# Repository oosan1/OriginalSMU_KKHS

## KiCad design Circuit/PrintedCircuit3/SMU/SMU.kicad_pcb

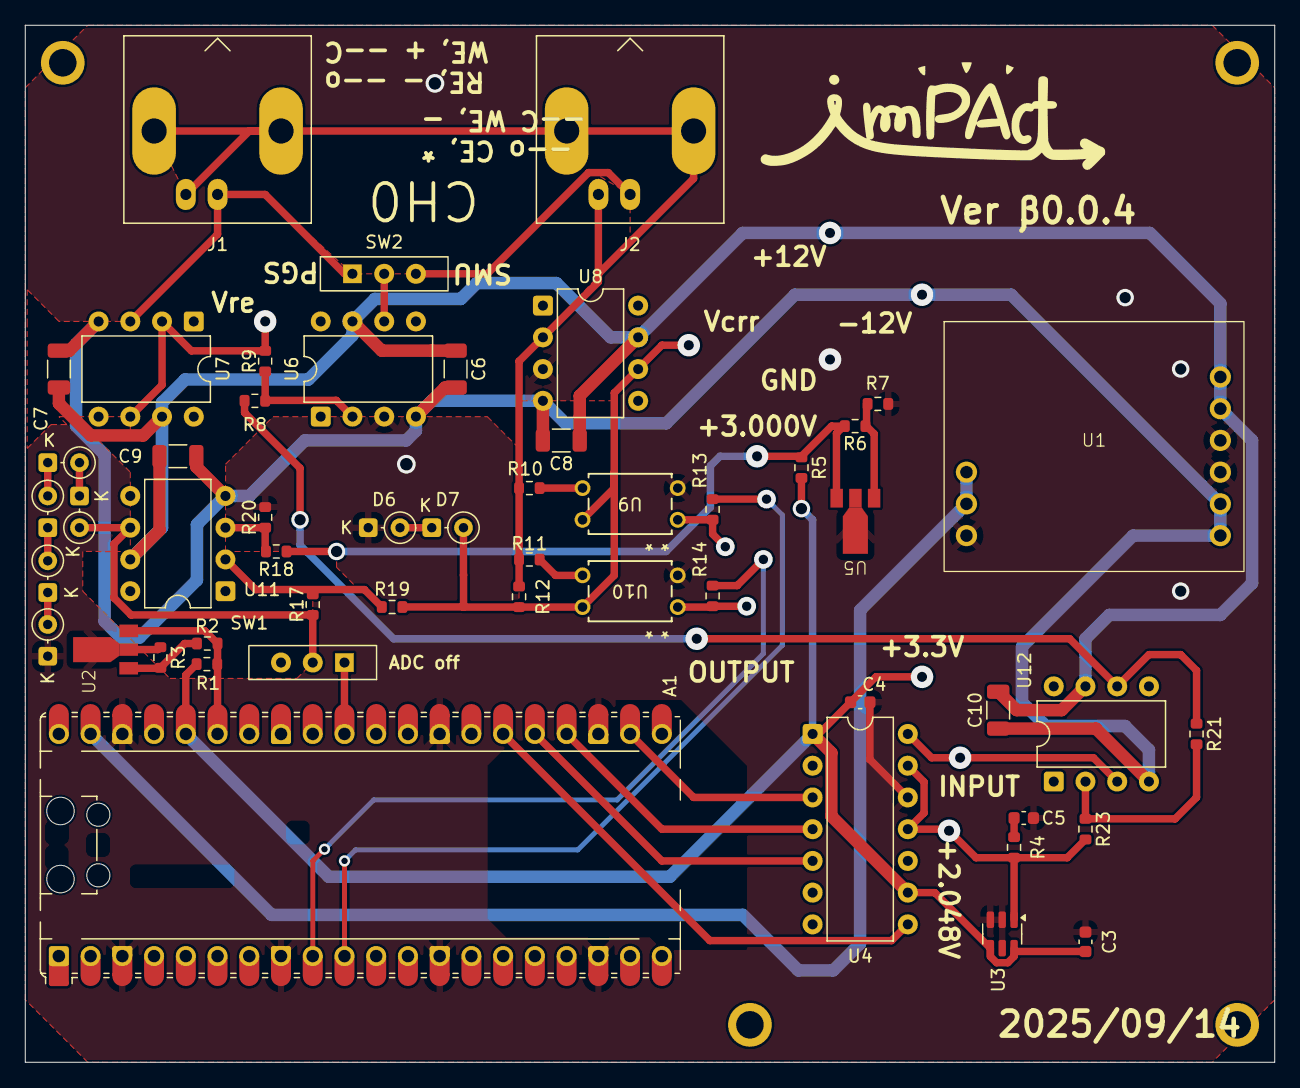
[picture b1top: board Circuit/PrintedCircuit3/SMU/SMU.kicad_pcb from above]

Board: 2 copper layers, 100.0 x 83.0 mm, 52 parts (0 on the bottom side), 40 nets.

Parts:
A1: RaspberryPi_Pico; RaspberryPi_Pico_Common_Unspecified
C3, C4, C5: 2.2u; C_0603_1608Metric
C6, C7, C8, C9, C10: 4.7u; C_1206_3216Metric
D1, D2, D3, D4, D5, D6, D7: D; D_DO-34_SOD68_P2.54mm_Vertical_KathodeUp
J1, J2: Conn_Coaxial; BNC_Amphenol_B6252HB-NPP3G-50_Horizontal
R1, R5: 51; R_0603_1608Metric
R2, R4, R6, R11, R13, R14: 1k; R_0603_1608Metric
R3, R7: 5.1k; R_0603_1608Metric
R8, R9, R12, R17, R19, R20, R21, R23: 10k; R_0603_1608Metric
R10: 100; R_0603_1608Metric
R18: 30k; R_0603_1608Metric
SW1, SW2: SW_SPDT; SW_Slide-03_Wuerth-WS-SLTV_10x2.5x6.4_P2.54mm
U1: TPS65131_kit
U2, U5: NJM1431AU
U3: MCP1501-20xCH; SOT-23-6
U4: MCP4922; DIP-14_W7.62mm
U6, U7, U8, U11, U12: OP07; DIP-8_W7.62mm
U9, U10: TLP241AF; DIP4_TOS

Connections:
3.0V_REF: R5.1, R6.1, R18.1, U5.3 (CATHODE)
+2.048V_REF: R4.1, R23.2, U3.1 (OUT), U4.11 (VrefB), U4.13 (VrefA)
+3.3V: A1.36 (3V3), C3.2, C4.1, R1.2, R5.2, U3.4 (~SHDN), U3.6 (VDD), U4.1 (Vdd), U4.9 (~SHDN)
+12V: C6.1, C7.1, C8.1, C9.2, C10.2, U1.4 (+OUT), U1.5 (+OUT), U6.7 (V+), U7.7 (V+), U8.7 (V+), U11.7 (V+), U12.7 (V+)
-12V: C6.2, C7.2, C8.2, C9.1, C10.1, U1.8 (-OUT), U1.9 (-OUT), U6.4 (V-), U7.4 (V-), U8.4 (V-), U11.4 (V-), U12.4 (V-)
/PotentioStatUnit/CE: SW2.2 (B), U6.6
/PotentioStatUnit/INPUT: R8.1, R21.1, U12.6
/PotentioStatUnit/RE: J1.1 (In), SW2.1 (A), U7.3 (+)
/PotentioStatUnit/Vcrr: D7.2 (A), R12.2, R19.2, U8.6, U9.4, U10.4
/PotentioStatUnit/Vre: R9.1, U7.2 (-), U7.6
/PotentioStatUnit/WE: J1.2 (Ext), J2.2 (Ext), R10.1, R11.1, R12.1, U8.2 (-)
/シフト増幅回路/INPUT: U4.14 (VA), U12.3 (+)
/反転回路/OUTPUT: D5.2 (A), R17.1, SW1.2 (B), U11.6
GND: A1.3 (GND), A1.8 (GND), A1.13 (GND), A1.18 (GND), A1.23 (GND), A1.28 (GND), A1.38 (GND), C3.1, C4.2, C5.1, D1.1 (K), D6.1 (K), R3.1, R7.1, R20.2, U1.3 (GND), U1.6 (GND), U1.7 (GND), U2.2 (ANODE), U3.2 (GND), U3.3 (GND), U3.5 (GND), U4.12 (Vss), U5.2 (ANODE), U6.3 (+), U8.3 (+), U9.2, U10.2
unnamed: A1.35 (ADC_VREF), R1.1, R2.1, U2.3 (CATHODE)
unnamed: A1.22 (GPIO17), U4.3 (~CS)
unnamed: A1.24 (GPIO18), U4.4 (SCK)
unnamed: A1.25 (GPIO19), U4.5 (SDI)
unnamed: A1.26 (GPIO20), U4.8 (~LDAC)
unnamed: A1.31 (GPIO26_ADC0), SW1.1 (A)
unnamed: C5.2, R4.2
unnamed: D1.2 (A), D2.1 (K)
unnamed: D2.2 (A), D3.1 (K)
unnamed: D3.2 (A), D4.1 (K)
unnamed: D4.2 (A), D5.1 (K)
unnamed: D6.2 (A), D7.1 (K)
unnamed: J2.1 (In), SW2.3 (C)
unnamed: R10.2, U9.3
unnamed: R11.2, U10.3
unnamed: R13.1, U9.1
unnamed: R14.1, U10.1
unnamed: R2.2, R3.2, U2.1 (REF)
unnamed: R6.2, R7.2, U5.1 (REF)
unnamed: R8.2, R9.2, U6.2 (-)
unnamed: R18.2, R20.1, U11.3 (+)
unnamed: R17.2, R19.1, U11.2 (-)
unnamed: R21.2, R23.1, U12.2 (-)
VSYS: A1.39 (VSYS), U1.1 (IN+), U1.2 (EN)
x1k: A1.9 (GPIO6), R14.2
x100: A1.10 (GPIO7), R13.2

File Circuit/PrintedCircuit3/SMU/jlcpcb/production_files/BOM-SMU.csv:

Comment,Designator,Footprint,LCSC,Quantity
1k,"R11,R13,R14,R2,R4,R6",R_0603_1608Metric,C21190,6
100,R10,R_0603_1608Metric,C22775,1
30k,R18,R_0603_1608Metric,C22984,1
5.1k,"R3,R7",R_0603_1608Metric,C23186,2
51,"R1,R5",R_0603_1608Metric,C23197,2
2.2u,"C3,C4,C5",C_0603_1608Metric,C23630,3
10k,"R12,R17,R19,R20,R21,R23,R8,R9",R_0603_1608Metric,C25804,8
4.7u,"C10,C6,C7,C8,C9",C_1206_3216Metric,C29823,5
OP07,U11,DIP-8_W7.62mm,,1
TLP241AF,U10,DIP4_TOS,,1
TLP241AF,U9,DIP4_TOS,,1
OP07,U8,DIP-8_W7.62mm,,1
OP07,U7,DIP-8_W7.62mm,,1
OP07,U6,DIP-8_W7.62mm,,1
~,U5,NJM1431AU,,1
MCP4922,U4,DIP-14_W7.62mm,,1
MCP1501-20xCH,U3,SOT-23-6,,1
~,U2,NJM1431AU,,1
TPS65131_kit,U1,TPS65131_kit,,1
SW_SPDT,SW2,SW_Slide-03_Wuerth-WS-SLTV_10x2.5x6.4_P2.54mm,,1
SW_SPDT,SW1,SW_Slide-03_Wuerth-WS-SLTV_10x2.5x6.4_P2.54mm,,1
Conn_Coaxial,J2,BNC_Amphenol_B6252HB-NPP3G-50_Horizontal,,1
Conn_Coaxial,J1,BNC_Amphenol_B6252HB-NPP3G-50_Horizontal,,1
D,D4,D_DO-34_SOD68_P2.54mm_Vertical_KathodeUp,,1
D,D3,D_DO-34_SOD68_P2.54mm_Vertical_KathodeUp,,1
D,D2,D_DO-34_SOD68_P2.54mm_Vertical_KathodeUp,,1
D,D1,D_DO-34_SOD68_P2.54mm_Vertical_KathodeUp,,1
RaspberryPi_Pico,A1,RaspberryPi_Pico_Common_Unspecified,,1
D,D7,D_DO-34_SOD68_P2.54mm_Vertical_KathodeUp,,1
D,D5,D_DO-34_SOD68_P2.54mm_Vertical_KathodeUp,,1
D,D6,D_DO-34_SOD68_P2.54mm_Vertical_KathodeUp,,1
OP07,U12,DIP-8_W7.62mm,,1

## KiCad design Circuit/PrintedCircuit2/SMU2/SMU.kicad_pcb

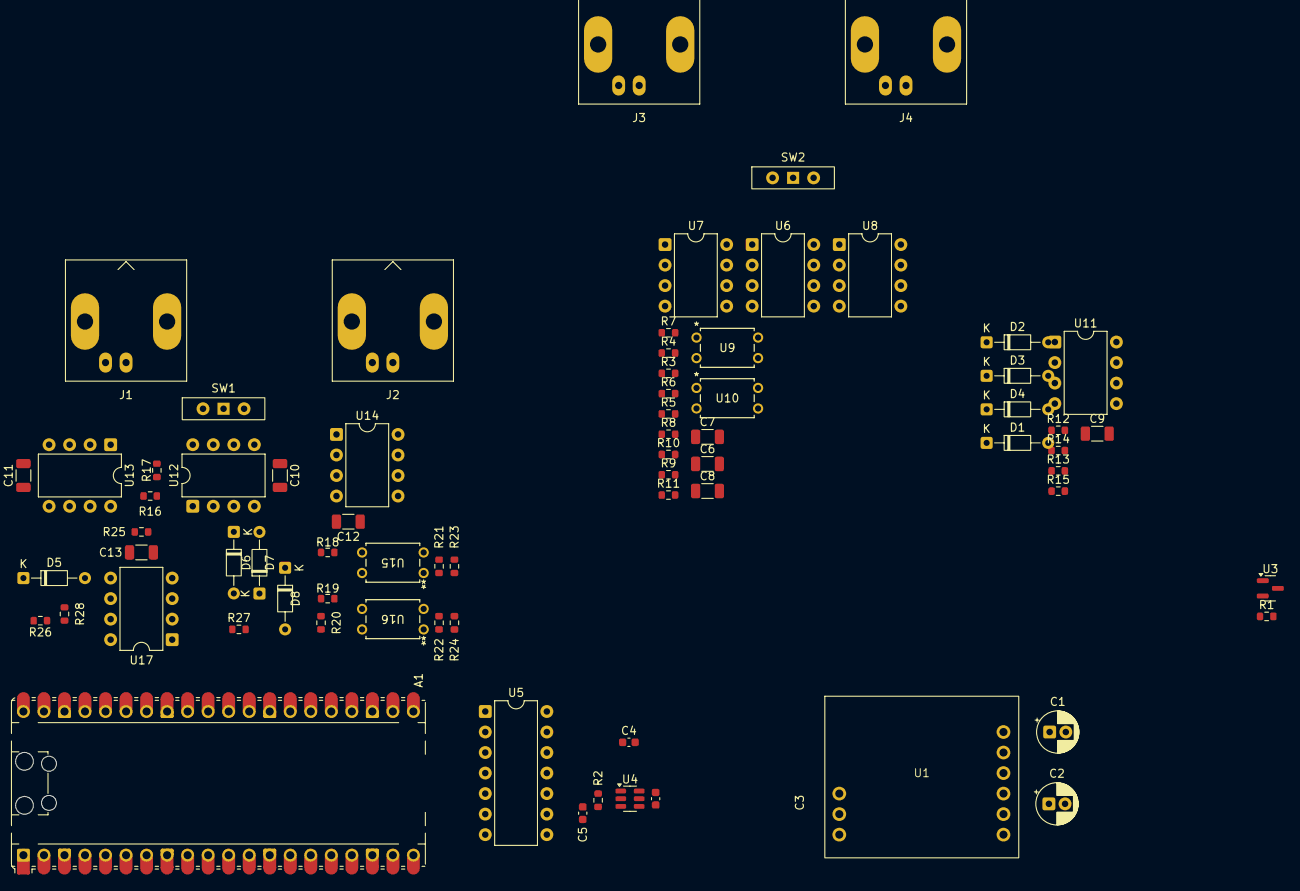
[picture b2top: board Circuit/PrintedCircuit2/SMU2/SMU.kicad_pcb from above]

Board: 6 copper layers, 73 parts (1 on the bottom side), 51 nets, no tracks yet.

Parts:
A1: RaspberryPi_Pico; RaspberryPi_Pico_Common_Unspecified
C1, C2: 100u; CP_Radial_D5.0mm_P2.00mm
C3, C4, C5: 2.2u; C_0603_1608Metric
C6, C7, C8, C9, C10, C11, C12, C13: 4.7u; C_1206_3216Metric
D1, D5: ZeD; D_DO-34_SOD68_P7.62mm_Horizontal
D2, D3, D4, D6, D7, D8: D; D_DO-34_SOD68_P7.62mm_Horizontal
J1, J2, J3, J4: Conn_Coaxial; BNC_Amphenol_B6252HB-NPP3G-50_Horizontal
R1: 200; R_0603_1608Metric
R2, R6, R19: 1k; R_0603_1608Metric
R3, R4, R5, R8, R9, R12, R14, R15, R16, R17, R18, R21, R22, R25, R27, R28: 10k; R_0603_1608Metric
R7, R20: 100; R_0603_1608Metric
R10, R11, R23, R24: 20k; R_0603_1608Metric
R13, R26: 30k; R_0603_1608Metric
SW1, SW2: SW_SPDT; SW_Slide-03_Wuerth-WS-SLTV_10x2.5x6.4_P2.54mm
U1: TPS65131_kit
U2, U3: LM4040DBZ-3; SOT-23
U4: MCP1501-20xCH; SOT-23-6
U5: MCP4922; DIP-14_W7.62mm
U6, U7, U8, U11, U12, U13, U14, U17: OP07; DIP-8_W7.62mm
U9, U10, U15, U16: TLP241AF; DIP4_TOS

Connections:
3.0V_REF: R1.1, R13.1, R26.1, U3.1 (K)
+3.3V: A1.36 (3V3), C3.2, C4.1, R1.2, U4.6 (VDD), U5.1 (Vdd), U5.9 (~SHDN)
+12V: C1.1, C6.1, C7.1, C8.1, C9.2, C10.1, C11.1, C12.1, C13.2, U1.4 (+OUT), U1.5 (+OUT), U6.7 (V+), U7.7 (V+), U8.7 (V+), U11.7 (V+), U12.7 (V+), U13.7 (V+), U14.7 (V+), U17.7 (V+)
-12V: C2.2, C6.2, C7.2, C8.2, C9.1, C10.2, C11.2, C12.2, C13.1, U1.8 (-OUT), U1.9 (-OUT), U6.4 (V-), U7.4 (V-), U8.4 (V-), U11.4 (V-), U12.4 (V-), U13.4 (V-), U14.4 (V-), U17.4 (V-)
/PotentioStatUnit1/CE: SW1.2 (B), U12.6
/PotentioStatUnit1/INPUT: R16.1, U5.14 (VA)
/PotentioStatUnit1/RE: J1.1 (In), SW1.1 (A), U13.3 (+)
/PotentioStatUnit1/Vcrr: D8.2 (A), R20.2, R27.2, U14.6, U15.4, U16.4
/PotentioStatUnit1/Vre: R17.1, U13.2 (-), U13.6
/PotentioStatUnit1/WE: J1.2 (Ext), J2.2 (Ext), R18.1, R19.1, R20.1, U14.2 (-)
/PotentioStatUnit/CE: SW2.2 (B), U6.6
/PotentioStatUnit/INPUT: R3.1, U5.10 (VB)
/PotentioStatUnit/RE: J3.1 (In), SW2.1 (A), U7.3 (+)
/PotentioStatUnit/Vcrr: D4.2 (A), R7.2, R14.2, U8.6, U9.4, U10.4
/PotentioStatUnit/Vre: R4.1, U7.2 (-), U7.6
/PotentioStatUnit/WE: J3.2 (Ext), J4.2 (Ext), R5.1, R6.1, R7.1, U8.2 (-)
/REF_+2.048V: R2.1, U4.1 (OUT), U5.11 (VrefB), U5.13 (VrefA)
/反転回路1/OUTPUT: A1.31 (GPIO26_ADC0), D5.2 (A), R25.1, U17.6
/反転回路/OUTPUT: A1.32 (GPIO27_ADC1), D1.2 (A), R12.1, U11.6
GND: A1.3 (GND), A1.8 (GND), A1.13 (GND), A1.18 (GND), A1.23 (GND), A1.28 (GND), A1.38 (GND), C1.2, C2.1, C3.1, C4.2, C5.1, D1.1 (K), D2.1 (K), D5.1 (K), D6.1 (K), R8.2, R9.1, R15.2, R21.2, R22.1, R28.2, U1.3 (GND), U1.6 (GND), U1.7 (GND), U2.2 (A), U3.2 (A), U4.2 (GND), U4.3 (GND), U4.4 (~SHDN), U4.5 (GND), U5.12 (Vss), U6.3 (+), U8.3 (+), U9.2, U10.2, U12.3 (+), U14.3 (+), U15.2, U16.2
unnamed: A1.35 (ADC_VREF), U2.1 (K)
unnamed: A1.22 (GPIO17), U5.3 (~CS)
unnamed: A1.24 (GPIO18), U5.4 (SCK)
unnamed: A1.25 (GPIO19), U5.5 (SDI)
unnamed: A1.26 (GPIO20), U5.8 (~LDAC)
unnamed: C5.2, R2.2
unnamed: D2.2 (A), D3.1 (K)
unnamed: D3.2 (A), D4.1 (K)
unnamed: D6.2 (A), D7.1 (K)
unnamed: D7.2 (A), D8.1 (K)
unnamed: J2.1 (In), SW1.3 (C)
unnamed: J4.1 (In), SW2.3 (C)
unnamed: R5.2, U9.3
unnamed: R6.2, U10.3
unnamed: R8.1, R10.2, U9.1
unnamed: R9.2, R11.1, U10.1
unnamed: R18.2, U15.3
unnamed: R19.2, U16.3
unnamed: R21.1, R23.2, U15.1
unnamed: R22.2, R24.1, U16.1
unnamed: R3.2, R4.2, U6.2 (-)
unnamed: R13.2, R15.1, U11.3 (+)
unnamed: R12.2, R14.1, U11.2 (-)
unnamed: R16.2, R17.2, U12.2 (-)
unnamed: R26.2, R28.1, U17.3 (+)
unnamed: R25.2, R27.1, U17.2 (-)
VSYS: A1.39 (VSYS), U1.1 (IN+), U1.2 (EN)
x1k_1: A1.9 (GPIO6), R24.2
x1k_2: A1.11 (GPIO8), R11.2
x10k_1: A1.10 (GPIO7), R23.1
x10k_2: A1.12 (GPIO9), R10.1

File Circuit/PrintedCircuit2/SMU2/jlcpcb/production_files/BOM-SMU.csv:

Comment,Designator,Footprint,LCSC,Quantity
1k,"R19,R2,R6",R_0603_1608Metric,C21190,3
100,"R20,R7",R_0603_1608Metric,C22775,2
30k,"R13,R26",R_0603_1608Metric,C22984,2
2.2u,"C3,C4,C5",C_0603_1608Metric,C23630,3
10k,"R12,R14,R15,R16,R17,R18,R21,R22,R25,R27,R28,R3,R4,R5,R8,R9",R_0603_1608Metric,C25804,16
4.7u,"C10,C11,C12,C13,C6,C7,C8,C9",C_1206_3216Metric,C29823,8
20k,"R10,R11,R23,R24",R_0603_1608Metric,C4184,4
OP07,U12,DIP-8_W7.62mm,,1
OP07,U11,DIP-8_W7.62mm,,1
TLP241AF,U10,DIP4_TOS,,1
TLP241AF,U9,DIP4_TOS,,1
OP07,U8,DIP-8_W7.62mm,,1
OP07,U7,DIP-8_W7.62mm,,1
OP07,U6,DIP-8_W7.62mm,,1
MCP4922,U5,DIP-14_W7.62mm,,1
MCP1501-20xCH,U4,SOT-23-6,,1
LM4040DBZ-3,U3,SOT-23,,1
LM4040DBZ-3,U2,SOT-23,,1
TPS65131_kit,U1,TPS65131_kit,,1
SW_SPDT,SW2,SW_Slide-03_Wuerth-WS-SLTV_10x2.5x6.4_P2.54mm,,1
SW_SPDT,SW1,SW_Slide-03_Wuerth-WS-SLTV_10x2.5x6.4_P2.54mm,,1
200,R1,R_0603_1608Metric,,1
Conn_Coaxial,J4,BNC_Amphenol_B6252HB-NPP3G-50_Horizontal,,1
Conn_Coaxial,J3,BNC_Amphenol_B6252HB-NPP3G-50_Horizontal,,1
Conn_Coaxial,J2,BNC_Amphenol_B6252HB-NPP3G-50_Horizontal,,1
Conn_Coaxial,J1,BNC_Amphenol_B6252HB-NPP3G-50_Horizontal,,1
D,D8,D_DO-34_SOD68_P7.62mm_Horizontal,,1
D,D7,D_DO-34_SOD68_P7.62mm_Horizontal,,1
D,D6,D_DO-34_SOD68_P7.62mm_Horizontal,,1
ZeD,D5,D_DO-34_SOD68_P7.62mm_Horizontal,,1
D,D4,D_DO-34_SOD68_P7.62mm_Horizontal,,1
D,D3,D_DO-34_SOD68_P7.62mm_Horizontal,,1
D,D2,D_DO-34_SOD68_P7.62mm_Horizontal,,1
ZeD,D1,D_DO-34_SOD68_P7.62mm_Horizontal,,1
100u,C2,CP_Radial_D5.0mm_P2.00mm,,1
100u,C1,CP_Radial_D5.0mm_P2.00mm,,1
SW_SPDT,SW4,SW_Slide-03_Wuerth-WS-SLTV_10x2.5x6.4_P2.54mm,,1
SW_SPDT,SW3,SW_Slide-03_Wuerth-WS-SLTV_10x2.5x6.4_P2.54mm,,1
TLP241AF,U16,DIP4_TOS,,1
OP07,U14,DIP-8_W7.62mm,,1
OP07,U17,DIP-8_W7.62mm,,1
TLP241AF,U15,DIP4_TOS,,1
OP07,U13,DIP-8_W7.62mm,,1
RaspberryPi_Pico,A1,RaspberryPi_Pico_Common_Unspecified,,1

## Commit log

2025-01-30 webクライアントを追加
2025-01-30 SMUの回路図等を追加
2025-01-30 シリアルの接続処理を追加
2025-01-30 シリアルコンソールの表示部分を追加
2025-01-30 シリアルの書き込み機能を追加
2025-01-30 シリアルの読み取り処理を追加(バグあり)
2025-02-02 SMUの各部分の配線を追加
2025-02-02 各部品の配線が完了。部品表を作り、発注書を作成。
2025-02-10 PWMのテスト用プログラム追加
2025-02-10 シリアル読み込みのバグ除去
2025-02-10 電気化学インピーダンス法用のシミュレーション回路を追加
2025-02-11 ファイル名変更(長すぎるとエラーが出るため)
2025-03-09 シリアル書き込みの不具合を修正
2025-03-09 ファイル構成を変更、シミュレーション用ファイルを追加
2025-03-17 実回路に合わせてシミュレーション回路を調整
2025-03-17 シリアル通信プロトコルに合わせてIVカーブ測定プログラムを変更
2025-03-17 コントロールパネル、グラフエリアを追加 IVカーブの測定、CSV出力をブラウザで完結可能に
2025-03-17 Kicadのバックアップファイルを追跡しないよう変更 Testフォルダは不要なため、削除
2025-03-19 gitignoreを修正
2025-03-19 プリント基板: 電源ユニット
2025-03-25 プリント基板: マイコン基板完成
2025-03-26 MicroPython版を更新
2025-03-26 C言語版を追加
2025-03-29 main3に校正機能を追加
2025-03-29 main3の校正機能にウェブクライアントとの連携機能を追加
2025-03-29 校正状態を表示するよう変更、displayをflexに変更
2025-03-30 シリアルコンソールの色変更機能追加 記録中のコンソール出力を無効にし、軽量化
2025-03-30 Control基板完成
2025-03-30 C版にコマンド解析を追加
2025-03-30 C版にADC,DAC制御コマンドを追加
2025-03-30 C版にIVsweepとIVcurveコマンド追加
2025-03-30 C版に対応
2025-03-30 C版完成、フラッシュ用に変更
2025-04-01 基盤にテストポイントを追加、SMUにDACとPSを追加
2025-04-02 保護回路のシミュレーションを追加
2025-04-03 SMUのプリント基板回路図完成
2025-04-04 フットプリント設定
2025-04-13 電気化学インピーダンス用アップデート
2025-04-24 EISコマンドを追加
2025-04-24 EISシミュレーションを追加
2025-04-26 WEとCEが逆転していた不具合を修正
2025-05-03 SMUのPCBを編集
2025-05-05 クライアントとマイコンにEISを追加
2025-05-10 クライアントをEISに対応
2025-05-10 マイコンのEISを反転回路に対応
2025-05-25 デザイン等を変更
2025-05-25 EISで周期性を向上
2025-05-25 EISの連続実行、colabでの自動解析に対応
2025-06-21 回路を更新
2025-06-21 回路を更新2
2025-06-22 β0.0.1の基板データが完成
2025-06-24 チャンネルを減らし、基板層数を削減
2025-06-25 実装を表に集中
2025-07-04 3Dモデルを更新
2025-07-12 ロゴ画像を追加
2025-07-14 β0.0.3
2025-07-18 保護回路を変更
2025-07-18 ADC.DAC電圧の可変に対応
2025-07-24 平均化機能を追加
2025-07-24 ケースを更新
2025-07-24 電流電圧変換抵抗の制御プログラムを追加
2025-08-05 測定待機時間を変更
2025-09-23 電圧データをstep表記かつ、生データへ統一。 ただし、未完成、実機では未検証
2025-09-23 ver0.0.4の基板データ完成
2025-09-24 マイコンにおいて、setVol, readVol, IVsweepコマンドをstep表記に統一。電圧の変化を可変ステップにすることに対応。他のコマンドは非推奨。
2025-09-24 step表記でのコマンド、ブラウザ上でのDAC, ADC設定の変更、可変電圧間隔のIVカーブ測定に対応。 EIS測定はまだ非対応
2025-09-27 マイコンが電流のレンジ操作に対応
2025-09-27 電流レンジの操作をクライアントに追加
2025-09-28 サイクリックモードにて、抵抗切り替え時間が長くなってしまう不具合を修正
2025-09-28 平均化機能をマイコンに追加
2025-09-28 平均化機能と安定用直列抵抗の補正機能をクライアントに追加
2025-10-05 クライアントソフトにバージョン表示を追加
2025-10-06 説明書を追加
2025-10-28 マイコン: 掃引方向の反転、リアルタイム送信に対応
2025-10-28 クライアント: 掃引方向の反転、リアルタイム送信に対応
2025-10-29 クライアント,マイコン：連続測定に対応
2025-10-30 IVカーブ測定時のボタン無効j化タイミングを調整
2025-10-30 オフラインモードを追加
2025-11-01 USBシリアルのカスタム名に対応
2025-11-01 32bitカウンターのオーバーフローにより、測定速度が不安定になる不具合を解消。ログに含まれる起動時間をより見やすく。
2025-11-01 picoへの書き込みを容易にするバッチファイルを追加
2025-11-01 デバッグ用命令を追加
2025-11-02 デバッグ用関数を追加
2025-11-02 RaspberrypiPicoのみを表示するよう、フィルターを追加
2025-11-02 接続時の例外処理を追加
2025-11-02 アイコン関係を追加
2025-11-02 機器バージョンの取得、定期的な機器状態の更新に対応。ファームウェアバージョンを追加。Cliant:β1.2.0、Firm:β1.0.0
2025-11-03 LEDの点灯動作を変更
2025-11-03 ヘッダーをよりシンプルに変更
2025-11-03 バージョン表記を更新
2025-11-18 bodyのpage-containerがはみ出ている不具合を修正
2025-11-18 ボード名を変更
2025-11-18 校正機能を追加
2026-03-12 主にケースの更新
2026-03-13 ファームウェアをより安定したEIS測定に対応
2026-03-13 クライアントをより安定したEIS測定に対応
2026-03-13 電源モード変更ピンをPico2用に更新
2026-03-14 テキストデコーダやそのパイプ処理を接続時のみ行うように変更
2026-03-14 前コミットの訂正
2026-03-15 古いコードを削除、受信データ数を表示
2026-03-15 古いコードを削除
2026-03-20 コードを整理
2026-03-20 バージョン番号を更新
2026-03-20 誤って消していたコードを修正
2026-03-25 フォルダを整理
2026-04-03 ドキュメントを整理
